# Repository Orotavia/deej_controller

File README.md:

# deej_controller

Custom controller for use with omriharel's [deej](https://github.com/omriharel/deej) software. Reads four rotary encoders with edge-driven interrupts to increment/decrement volume per channel. Volume data is sent over serial to the FT230X which appears as a serial port on the host PC. 

Known issues:
* FT230X and MCP1700 both output 3.3V onto the same rail. Need to separate to prevent voltage mis-match and resultant backwards current flow. 
* 5.3x10.2 SOIC16W footprints for SN74HC595N shift registers are too wide - Need to switch to SOIC16
* LED Bargraph footprints are too wide - Need to reduce row-to-row spacing, must likely by 2.54mm or some multiple

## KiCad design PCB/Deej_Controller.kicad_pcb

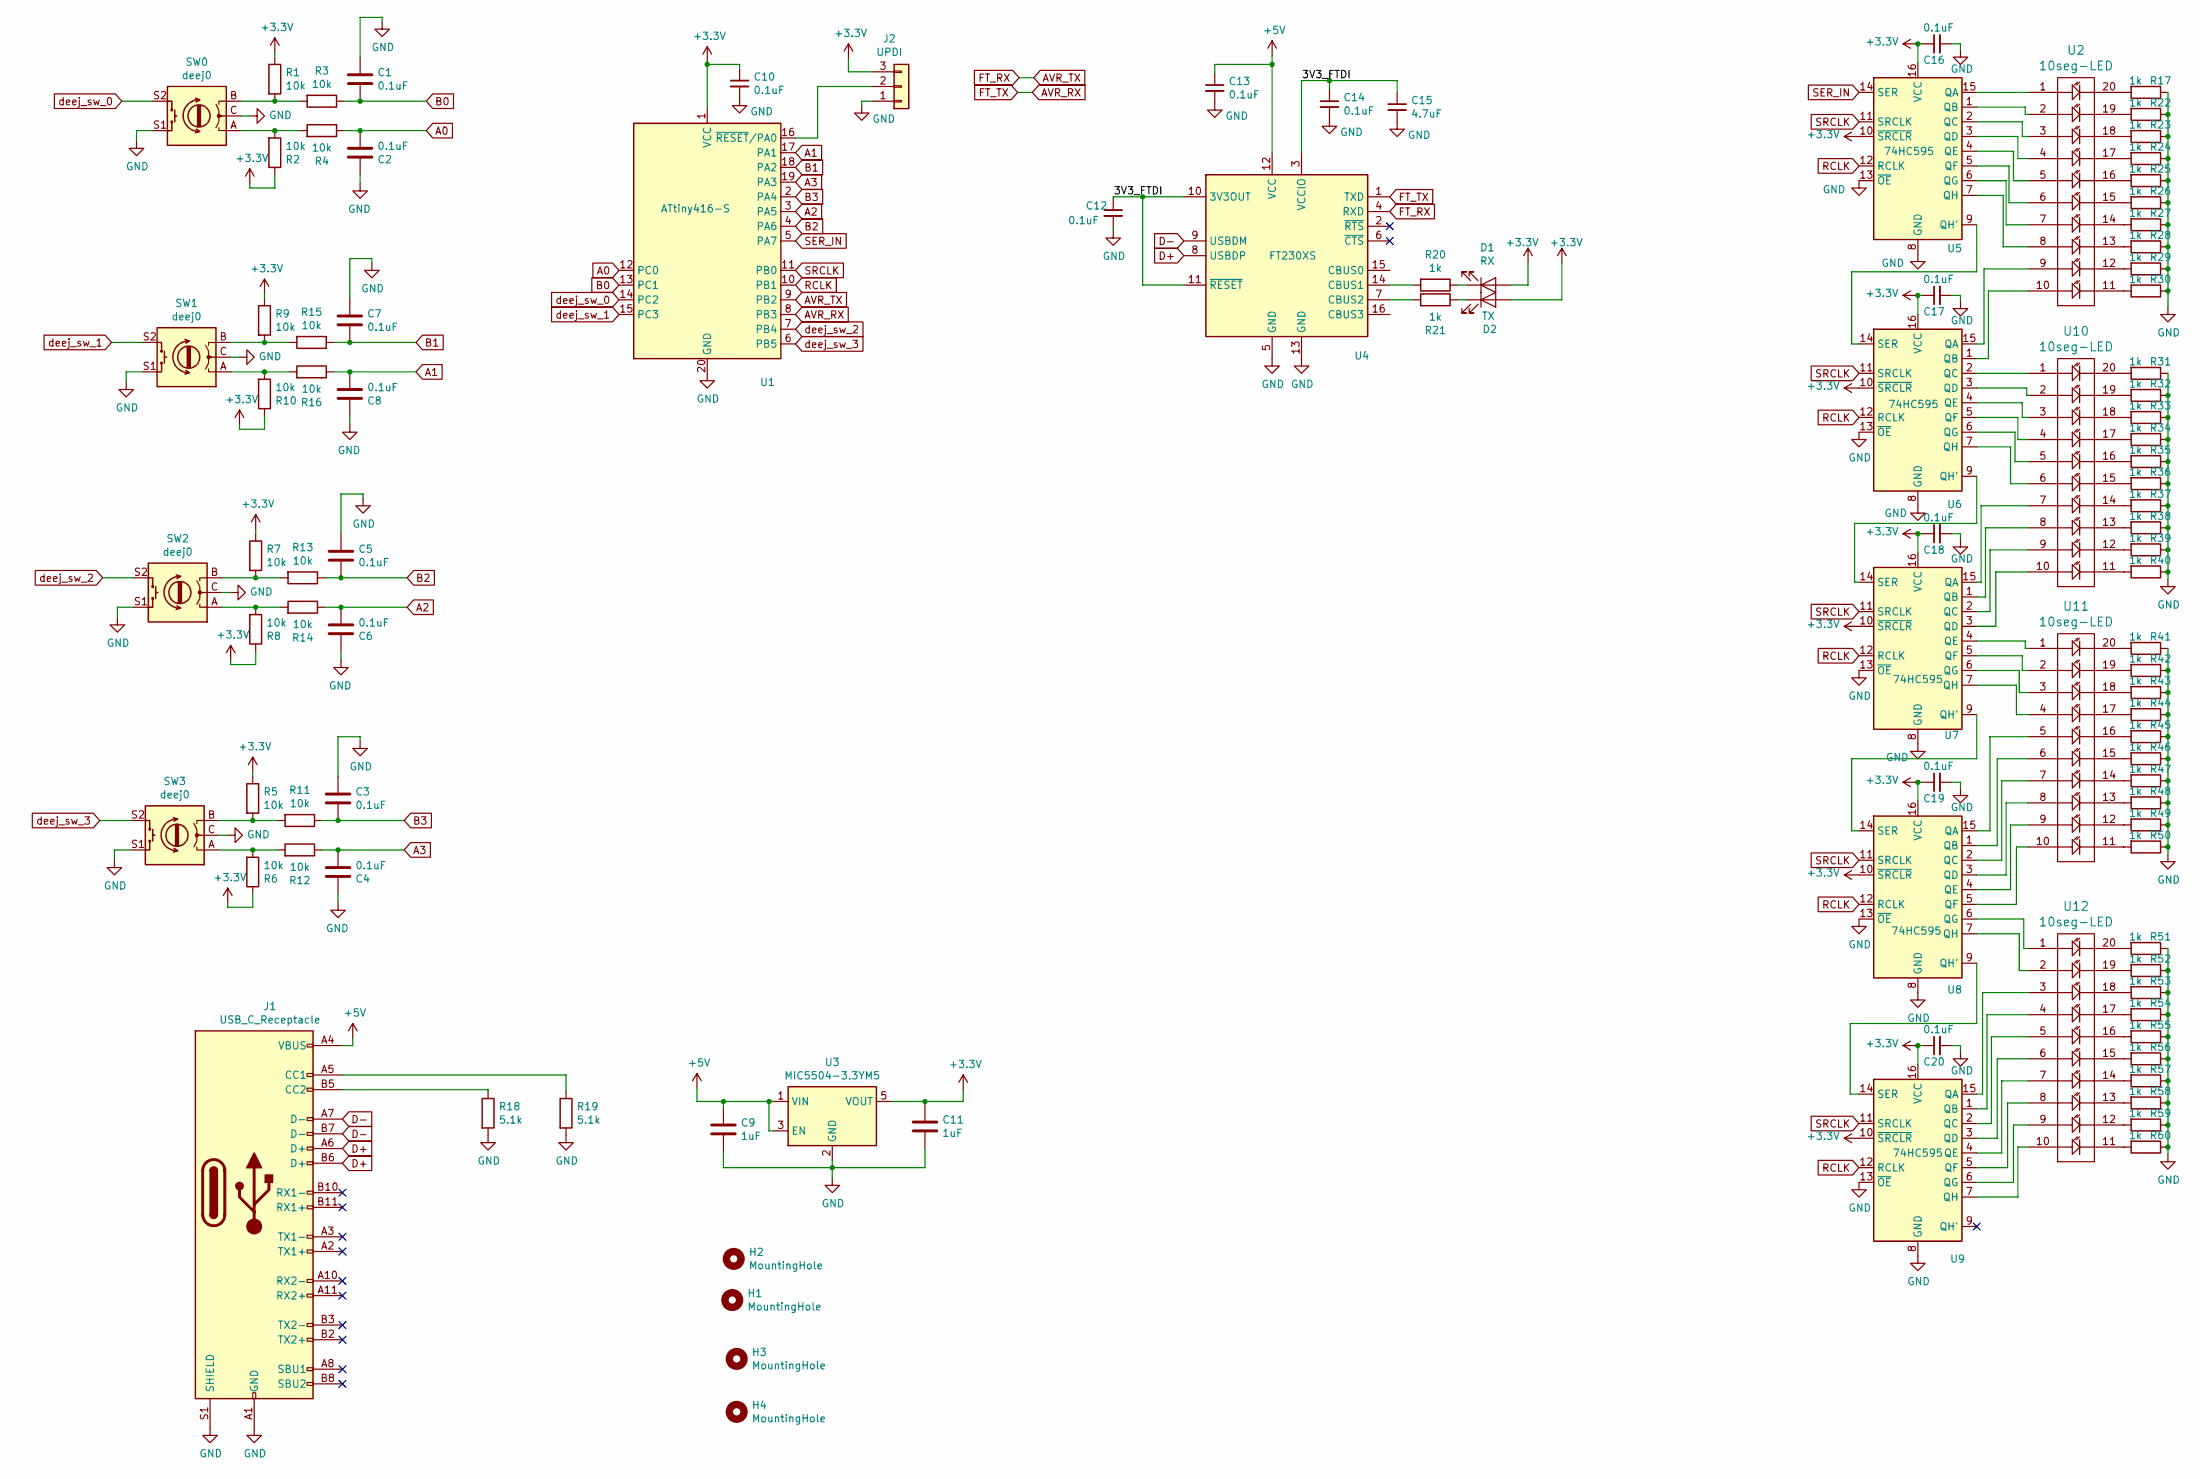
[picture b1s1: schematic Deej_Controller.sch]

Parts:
C1, C2, C3, C4, C5, C6, C7, C8, C10, C12, C13, C14, C16, C17, C18, C19, C20: 0.1uF; C_0603
C9, C11: 1uF; C_0603
C15: 4.7uF; C_0603
D1: RX; LED_0603
D2: TX; LED_0603
H1, H2, H3, H4: MountingHole; MountingHole_3.2mm_M3_DIN965_Pad
J1: USB_C_Receptacle; USB_C_GCT_ThruHole
J2: UPDI; UPDI_Header_2.54_smd
R1, R2, R3, R4, R5, R6, R7, R8, R9, R10, R11, R12, R13, R14, R15, R16: 10k; R_0603
R17, R20, R21, R22, R23, R24, R25, R26, R27, R28, R29, R30, R31, R32, R33, R34, R35, R36, R37, R38, R39, R40, R41, R42, R43, R44, R45, R46, R47, R48, R49, R50, R51, R52, R53, R54, R55, R56, R57, R58, R59, R60: 1k; R_0603
R18, R19: 5.1k; R_0603
SW0, SW1, SW2, SW3: deej0; PEC11R-Encoder
U1: ATtiny416-S; SOIC-20W_7.5x12.8mm_Pitch1.27mm
U2, U10, U11, U12: 10seg-LED; 10Segment_LED
U3: MIC5504-3.3YM5; SOT-23-5
U4: FT230XS; SSOP-16_3.9x4.9mm_Pitch0.635mm
U5, U6, U7, U8, U9: 74HC595; SOIC-16W_5.3x10.2mm_Pitch1.27mm

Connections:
+5V: C9.1, C13.1, J1.A4 (VBUS), J1.A9 (VBUS), J1.B4 (VBUS), J1.B9 (VBUS), U3.1 (VIN), U3.3 (EN), U4.12 (VCC)
A0: C2.1, R4.1, U1.12 (PC0)
A1: C8.1, R16.1, U1.17 (PA1)
A2: C6.1, R14.1, U1.3 (PA5)
A3: C4.1, R12.1, U1.19 (PA3)
AVR_RX: U1.8 (PB3), U4.1 (TXD)
AVR_TX: U1.9 (PB2), U4.4 (RXD)
B0: C1.1, R3.1, U1.13 (PC1)
B1: C7.1, R15.1, U1.18 (PA2)
B2: C5.1, R13.1, U1.4 (PA6)
B3: C3.1, R11.1, U1.2 (PA4)
D+: J1.A6 (D+), J1.B6 (D+), U4.8 (USBDP)
D-: J1.A7 (D-), J1.B7 (D-), U4.9 (USBDM)
GND: C1.2, C2.2, C3.2, C4.2, C5.2, C6.2, C7.2, C8.2, C9.2, C10.2, C11.2, C12.2, C13.2, C14.2, C15.2, C16.2, C17.2, C18.2, C19.2, C20.2, J1.A1 (GND), J1.A12 (GND), J1.B1 (GND), J1.B12 (GND), J1.S1 (SHIELD), J2.1, R17.1, R18.2, R19.2, R22.1, R23.1, R24.1, R25.1, R26.1, R27.1, R28.1, R29.1, R30.1, R31.1, R32.1, R33.1, R34.1, R35.1, R36.1, R37.1, R38.1, R39.1, R40.1, R41.1, R42.1, R43.1, R44.1, R45.1, R46.1, R47.1, R48.1, R49.1, R50.1, R51.1, R52.1, R53.1, R54.1, R55.1, R56.1, R57.1, R58.1, R59.1, R60.1, SW0.C, SW0.S1, SW1.C, SW1.S1, SW2.C, SW2.S1, SW3.C, SW3.S1, U1.20 (GND), U3.2 (GND), U4.5 (GND), U4.13 (GND), U5.8 (GND), U5.13 (~OE), U6.8 (GND), U6.13 (~OE), U7.8 (GND), U7.13 (~OE), U8.8 (GND), U8.13 (~OE), U9.8 (GND), U9.13 (~OE)
unnamed: D1.1 (K), R20.1
unnamed: D2.1 (K), R21.1
unnamed: J1.A5 (CC1), R19.1
unnamed: J1.B5 (CC2), R18.1
unnamed: J2.2, U1.16 (~RESET~/PA0)
unnamed: R1.2, R3.2, SW0.B
unnamed: R2.2, R4.2, SW0.A
unnamed: R10.2, R16.2, SW1.A
unnamed: R5.2, R11.2, SW3.B
unnamed: R6.2, R12.2, SW3.A
unnamed: R7.2, R13.2, SW2.B
unnamed: R8.2, R14.2, SW2.A
unnamed: R9.2, R15.2, SW1.B
unnamed: R17.2, U2.20
unnamed: R20.2, U4.14 (CBUS1)
unnamed: R21.2, U4.7 (CBUS2)
unnamed: R22.2, U2.19
unnamed: R23.2, U2.18
unnamed: R24.2, U2.17
unnamed: R25.2, U2.16
unnamed: R26.2, U2.15
unnamed: R27.2, U2.14
unnamed: R28.2, U2.13
unnamed: R29.2, U2.12
unnamed: R30.2, U2.11
unnamed: R31.2, U10.20
unnamed: R32.2, U10.19
unnamed: R33.2, U10.18
unnamed: R34.2, U10.17
unnamed: R35.2, U10.16
unnamed: R36.2, U10.15
unnamed: R37.2, U10.14
unnamed: R38.2, U10.13
unnamed: R39.2, U10.12
unnamed: R40.2, U10.11
unnamed: R41.2, U11.20
unnamed: R42.2, U11.19
unnamed: R43.2, U11.18
unnamed: R44.2, U11.17
unnamed: R45.2, U11.16
unnamed: R46.2, U11.15
unnamed: R47.2, U11.14
unnamed: R48.2, U11.13
unnamed: R49.2, U11.12
unnamed: R50.2, U11.11
unnamed: R51.2, U12.20
unnamed: R52.2, U12.19
unnamed: R53.2, U12.18
unnamed: R54.2, U12.17
unnamed: R55.2, U12.16
unnamed: R56.2, U12.15
unnamed: R57.2, U12.14
unnamed: R58.2, U12.13
unnamed: R59.2, U12.12
unnamed: R60.2, U12.11
unnamed: U2.1, U5.15 (QA)
unnamed: U2.2, U5.1 (QB)
unnamed: U2.3, U5.2 (QC)
unnamed: U2.4, U5.3 (QD)
unnamed: U2.5, U5.4 (QE)
unnamed: U2.6, U5.5 (QF)
unnamed: U2.7, U5.6 (QG)
unnamed: U2.8, U5.7 (QH)
unnamed: U2.9, U6.15 (QA)
unnamed: U2.10, U6.1 (QB)
unnamed: U5.9 (QH'), U6.14 (SER)
unnamed: U6.9 (QH'), U7.14 (SER)
unnamed: U7.9 (QH'), U8.14 (SER)
unnamed: U8.9 (QH'), U9.14 (SER)
unnamed: U6.2 (QC), U10.1
unnamed: U6.3 (QD), U10.2
unnamed: U6.4 (QE), U10.3
unnamed: U6.5 (QF), U10.4
unnamed: U6.6 (QG), U10.5
unnamed: U6.7 (QH), U10.6
unnamed: U7.15 (QA), U10.7
unnamed: U7.1 (QB), U10.8
unnamed: U7.2 (QC), U10.9
unnamed: U7.3 (QD), U10.10
unnamed: U7.4 (QE), U11.1
unnamed: U7.5 (QF), U11.2
unnamed: U7.6 (QG), U11.3
unnamed: U7.7 (QH), U11.4
unnamed: U8.15 (QA), U11.5
unnamed: U8.1 (QB), U11.6
unnamed: U8.2 (QC), U11.7
unnamed: U8.3 (QD), U11.8
unnamed: U8.4 (QE), U11.9
unnamed: U8.5 (QF), U11.10
unnamed: U8.6 (QG), U12.1
unnamed: U8.7 (QH), U12.2
unnamed: U9.15 (QA), U12.3
unnamed: U9.1 (QB), U12.4
unnamed: U9.2 (QC), U12.5
unnamed: U9.3 (QD), U12.6
unnamed: U9.4 (QE), U12.7
unnamed: U9.5 (QF), U12.8
unnamed: U9.6 (QG), U12.9
unnamed: U9.7 (QH), U12.10
RCLK: U1.10 (PB1), U5.12 (RCLK), U6.12 (RCLK), U7.12 (RCLK), U8.12 (RCLK), U9.12 (RCLK)
SER_IN: U1.5 (PA7), U5.14 (SER)
SRCLK: U1.11 (PB0), U5.11 (SRCLK), U6.11 (SRCLK), U7.11 (SRCLK), U8.11 (SRCLK), U9.11 (SRCLK)
deej_sw_0: SW0.S2, U1.14 (PC2)
deej_sw_1: SW1.S2, U1.15 (PC3)
deej_sw_2: SW2.S2, U1.7 (PB4)
deej_sw_3: SW3.S2, U1.6 (PB5)

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
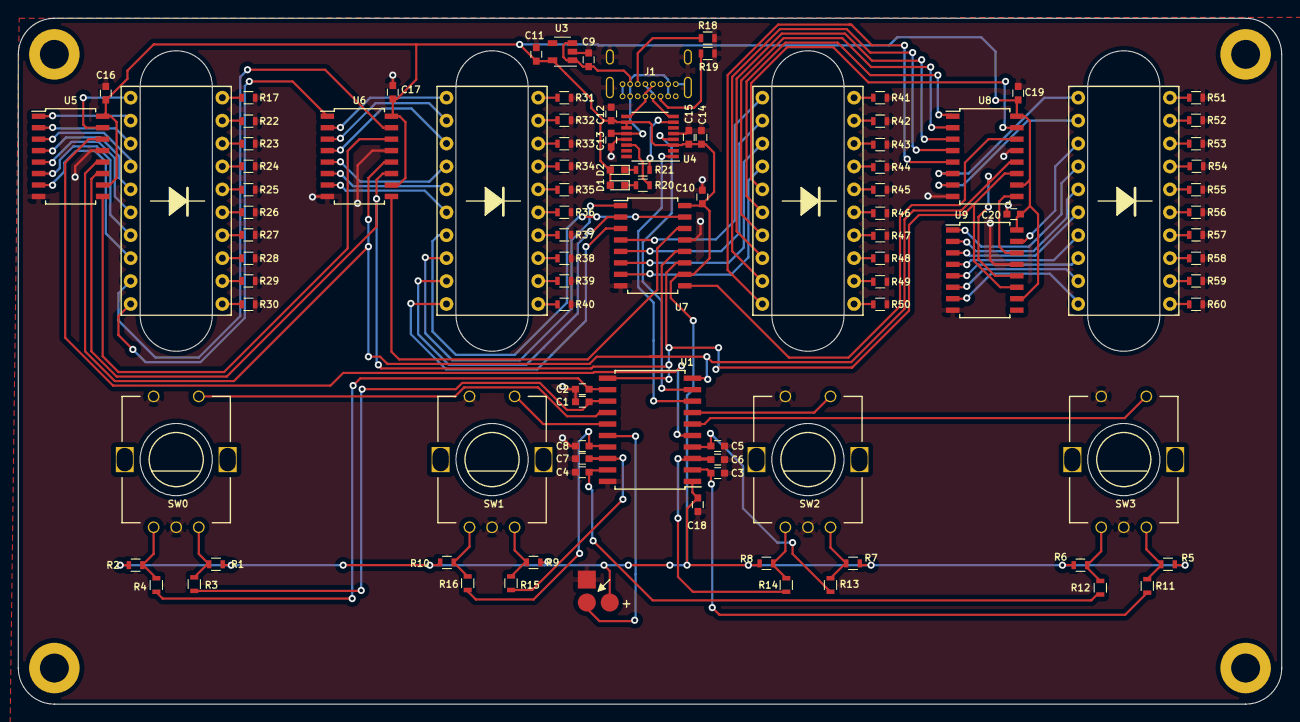
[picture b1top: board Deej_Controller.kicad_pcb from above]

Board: 2 copper layers, 140.0 x 76.0 mm, 104 parts (0 on the bottom side), 121 nets.

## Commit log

2021-09-24 added pic
